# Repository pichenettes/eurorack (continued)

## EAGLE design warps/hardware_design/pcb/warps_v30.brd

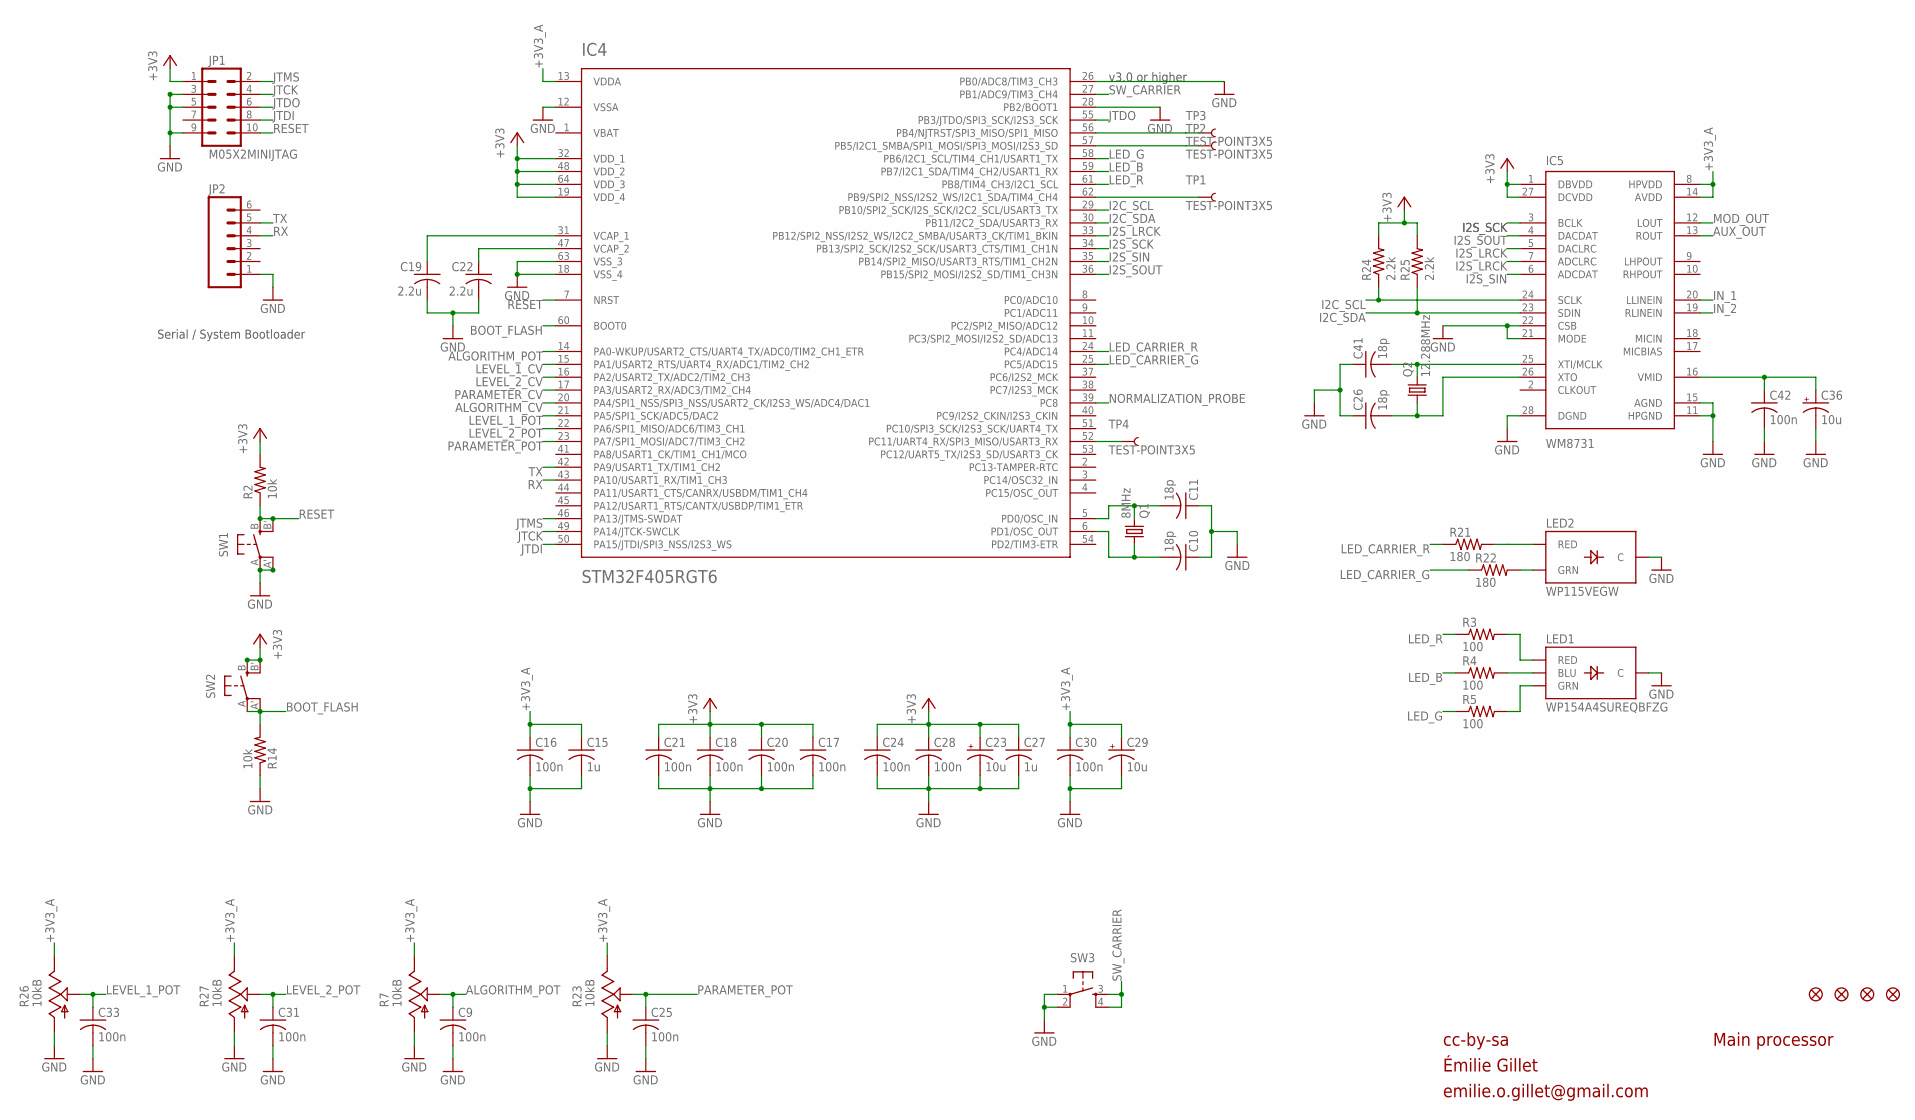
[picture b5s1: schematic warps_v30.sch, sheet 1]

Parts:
C9, C16, C17, C18, C20, C21, C24, C25, C28, C30, C31, C33, C42: 100n; C0603
C10, C11, C26, C41: 18p; C0603
C15, C27: 1u; C0603
C19, C22: 2.2u; C0805
C23, C29, C36: 10u; PANASONIC_A
F1, F2, F3, F4: FIDUCIAL1X2; FIDUCIAL-1X2
IC4: STM32F405RGT6; TQFP-10X10-64
IC5: WM8731; SSOP28
JP1: M05X2MINIJTAG; 2X5-1.27
JP2: M06SIP; 1X06
LED1: WP154A4SUREQBFZG; LED-TRICOLOR-THROUGHHOLE
LED2: WP115VEGW; LED-BICOLOR-THROUGHHOLE
Q1: 8MHz; HC49UP
Q2: 12.288MHz; HC49UP
R2, R14: 10k; R0603
R3, R4, R5: 100; R0603
R7, R23: 10kB; ALPS_POT_VERTICAL_PS
R21, R22: 180; R0603
R24, R25: 2.2k; R0603
R26, R27: 10kB; ALPS_POT_VERTICAL
SW1, SW2: EVQQ2; EVQ-Q2
SW3: TAC_SWITCHPTH; TACTILE-PTH
TP1, TP2, TP3, TP4: TEST-POINT3X5; PAD.03X.05

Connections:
+3V3: C17.1, C18.1, C20.1, C21.1, C23.+, C24.1, C27.1, C28.1, IC4.19 (VDD_4), IC4.32 (VDD_1), IC4.48 (VDD_2), IC4.64 (VDD_3), IC5.1 (DBVDD), IC5.27 (DCVDD), JP1.1, R2.2, R24.2, R25.2, SW2.B (S), SW2.B' (S1); also elsewhere on the board
+3V3_A: C15.1, C16.1, C29.+, C30.1, IC4.13 (VDDA), IC5.8 (HPVDD), IC5.14 (AVDD), R7.P$1 (E), R23.P$1 (E), R26.P$1 (E), R27.P$1 (E); also elsewhere on the board
ALGORITHM_CV: IC4.20 (PA4/SPI1_NSS/SPI3_NSS/USART2_CK/I2S3_WS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); also elsewhere on the board
ALGORITHM_POT: C9.1, IC4.14 (PA0-WKUP/USART2_CTS/UART4_TX/ADC0/TIM2_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), R7.P$2 (S)
AUX_OUT: IC5.13 (ROUT); also elsewhere on the board
BOOT_FLASH: IC4.60 (BOOT0), R14.2, SW2.A, SW2.A' (P1)
GND: C9.2, C10.1, C11.1, C15.2, C16.2, C17.2, C18.2, C19.2, C20.2, C21.2, C22.2, C23.-, C24.2, C25.2, C26.1, C27.2, C28.2, C29.-, C30.2, C31.2, C33.2, C36.-, C41.1, C42.2, IC4.12 (VSSA), IC4.18 (VSS_4), IC4.26 (PB0/ADC8/TIM3_CH3), IC4.28 (PB2/BOOT1), IC4.63 (VSS_3), IC5.11 (HPGND), IC5.15 (AGND), IC5.21 (MODE), IC5.22 (CSB), IC5.28 (DGND), JP1.3, JP1.5, JP1.9, JP2.1, LED1.GND (C), LED2.2 (C), R7.P$3 (A), R14.1, R23.P$3 (A), R26.P$3 (A), R27.P$3 (A), SW1.A, SW1.A' (P1), SW3.1, SW3.2; also elsewhere on the board
I2C_SCL: IC4.29 (PB10/SPI2_SCK/I2S_SCK/I2C2_SCL/USART3_TX), IC5.24 (SCLK), R24.1
I2C_SDA: IC4.30 (PB11/I2C2_SDA/USART3_RX), IC5.23 (SDIN), R25.1
I2S_LRCK: IC4.33 (PB12/SPI2_NSS/I2S2_WS/I2C2_SMBA/USART3_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), IC5.5 (DACLRC), IC5.7 (ADCLRC)
I2S_SCK: IC4.34 (PB13/SPI2_SCK/I2S2_SCK/USART3_CTS/TIM1_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), IC5.3 (BCLK)
I2S_SIN: IC4.35 (PB14/SPI2_MISO/USART3_RTS/TIM1_CH2N), IC5.6 (ADCDAT)
I2S_SOUT: IC4.36 (PB15/SPI2_MOSI/I2S2_SD/TIM1_CH3N), IC5.4 (DACDAT)
IN_1: IC5.20 (LLINEIN); also elsewhere on the board
IN_2: IC5.19 (RLINEIN); also elsewhere on the board
JTCK: IC4.49 (PA14/JTCK-SWCLK), JP1.4
JTDI: IC4.50 (PA15/JTDI/SPI3_NSS/I2S3_WS), JP1.8
JTDO: IC4.55 (PB3/JTDO/SPI3_SCK/I2S3_SCK), JP1.6
JTMS: IC4.46 (PA13/JTMS-SWDAT), JP1.2
LED_B: IC4.59 (PB7/I2C1_SDA/TIM4_CH2/USART1_RX), R4.1
LED_CARRIER_G: IC4.25 (PC5/ADC15), R22.1
LED_CARRIER_R: IC4.24 (PC4/ADC14), R21.1
LED_G: IC4.58 (PB6/I2C1_SCL/TIM4_CH1/USART1_TX), R5.1
LED_R: IC4.61 (PB8/TIM4_CH3/I2C1_SCL), R3.1
LEVEL_1_CV: IC4.15 (PA1/USART2_RTS/UART4_RX/ADC1/TIM2_CH2); also elsewhere on the board
LEVEL_1_POT: C33.1, IC4.21 (PA5/SPI1_SCK/ADC5/DAC2), R26.P$2 (S)
LEVEL_2_CV: IC4.16 (PA2/USART2_TX/ADC2/TIM2_CH3); also elsewhere on the board
LEVEL_2_POT: C31.1, IC4.22 (PA6/SPI1_MISO/ADC6/TIM3_CH1), R27.P$2 (S)
MOD_OUT: IC5.12 (LOUT); also elsewhere on the board
unnamed: LED2.3 (RED), R21.2
unnamed: C11.2, IC4.5 (PD0/OSC_IN), Q1.2
unnamed: C10.2, IC4.6 (PD1/OSC_OUT), Q1.1
unnamed: C22.1, IC4.47 (VCAP_2)
unnamed: LED2.1 (GRN), R22.2
unnamed: C36.+, C42.1, IC5.16 (VMID)
unnamed: C19.1, IC4.31 (VCAP_1)
unnamed: IC4.56 (PB4/NJTRST/SPI3_MISO/SPI1_MISO), TP3.P$1
unnamed: IC4.57 (PB5/I2C1_SMBA/SPI1_MOSI/SPI3_MOSI/I2S3_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), TP2.P$1
unnamed: IC4.52 (PC11/UART4_RX/SPI3_MISO/USART3_RX), TP4.P$1
unnamed: IC4.62 (PB9/SPI2_NSS/I2S2_WS/I2C1_SDA/TIM4_CH4), TP1.P$1
unnamed: LED1.RED, R3.2
unnamed: LED1.BLU, R4.2
unnamed: LED1.GRN, R5.2
unnamed: C41.2, IC5.25 (XTI/MCLK), Q2.2
unnamed: C26.2, IC5.26 (XTO), Q2.1
NORMALIZATION_PROBE: IC4.39 (PC8); also elsewhere on the board
PARAMETER_CV: IC4.17 (PA3/USART2_RX/ADC3/TIM2_CH4); also elsewhere on the board
PARAMETER_POT: C25.1, IC4.23 (PA7/SPI1_MOSI/ADC7/TIM3_CH2), R23.P$2 (S)
RESET: IC4.7 (NRST), JP1.10, R2.1, SW1.B (S), SW1.B' (S1)
RX: IC4.43 (PA10/USART1_RX/TIM1_CH3), JP2.4
SW_CARRIER: IC4.27 (PB1/ADC9/TIM3_CH4), SW3.3, SW3.4
TX: IC4.42 (PA9/USART1_TX/TIM1_CH2), JP2.5
VBAT: IC4.1 (VBAT)

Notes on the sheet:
cc-by-sa
Main processor
Serial / System Bootloader
v3.0 or higher
Émilie Gillet
emilie.o.gillet@gmail.com

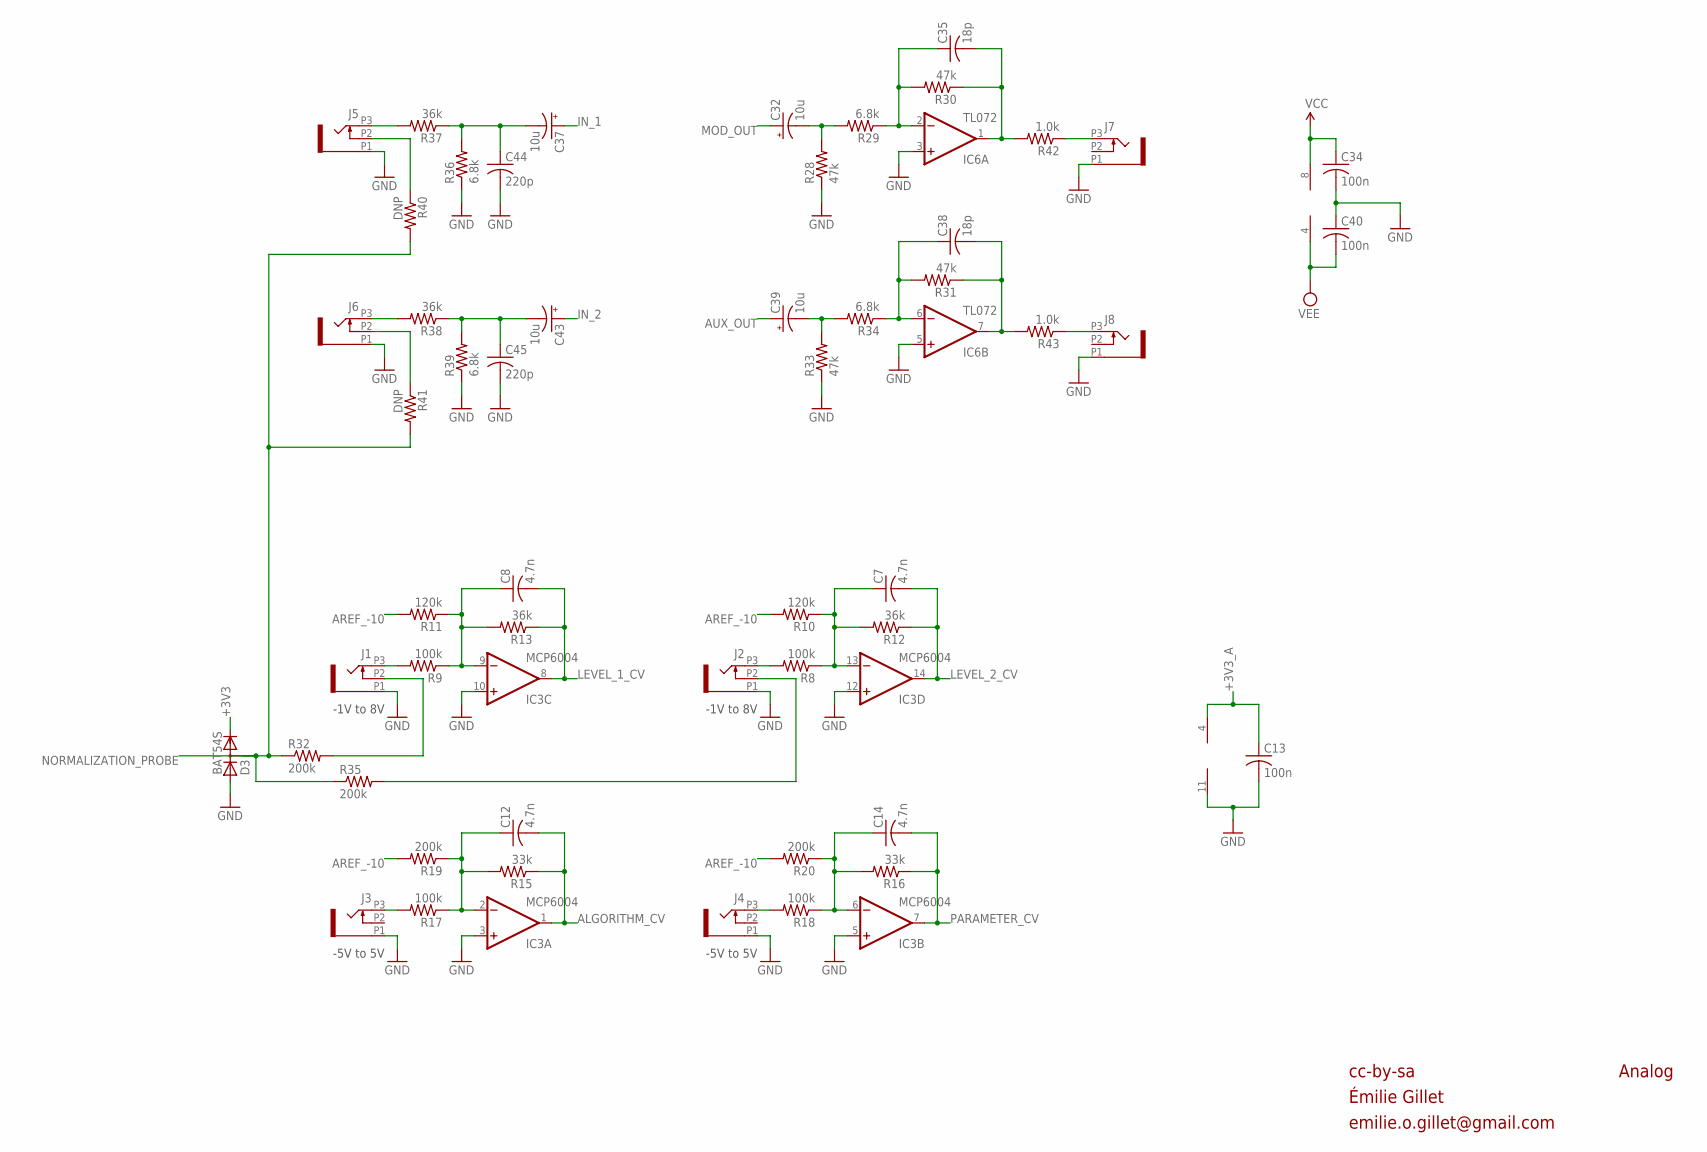
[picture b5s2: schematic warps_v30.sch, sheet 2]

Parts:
C7, C8, C12, C14: 4.7n; C0603
C13, C34, C40: 100n; C0603
C32, C37, C39, C43: 10u; PANASONIC_A
C35, C38: 18p; C0603
C44, C45: 220p; C0603
D3: BAT54S; SOT23
IC3: MCP6004; SO14
IC6: TL072; SO08
J1, J2, J3, J4, J5, J6, J7, J8: PJ301_THONKICONN6; WQP_PJ_301M6
R8, R9, R17, R18: 100k; R0603
R10, R11: 120k; R0603
R12, R13, R37, R38: 36k; R0603
R15, R16: 33k; R0603
R19, R20, R32, R35: 200k; R0603
R28, R30, R31, R33: 47k; R0603
R29, R34, R36, R39: 6.8k; R0603
R40, R41: DNP; R0603
R42, R43: 1.0k; R0603

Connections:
+3V3: D3.2 (C); also elsewhere on the board
+3V3_A: C13.1, IC3.4 (V+); also elsewhere on the board
ALGORITHM_CV: C12.2, IC3.1 (OUT), R15.1; also elsewhere on the board
AREF_-10: R10.2, R11.2, R19.2, R20.2; also elsewhere on the board
AUX_OUT: C39.+; also elsewhere on the board
GND: C13.2, C34.2, C40.1, C44.2, C45.2, D3.1 (A), IC3.3 (+IN), IC3.5 (+IN), IC3.10 (+IN), IC3.11 (V-), IC3.12 (+IN), IC6.3 (+IN), IC6.5 (+IN), J1.P1 (1), J2.P1 (1), J3.P1 (1), J4.P1 (1), J5.P1 (1), J6.P1 (1), J7.P1 (1), J8.P1 (1), R28.1, R33.1, R36.1, R39.1; also elsewhere on the board
IN_1: C37.+; also elsewhere on the board
IN_2: C43.+; also elsewhere on the board
LEVEL_1_CV: C8.2, IC3.8 (OUT), R13.1; also elsewhere on the board
LEVEL_2_CV: C7.2, IC3.14 (OUT), R12.1; also elsewhere on the board
MOD_OUT: C32.+; also elsewhere on the board
unnamed: J1.P3 (3), R9.2
unnamed: C8.1, IC3.9 (-IN), R9.1, R11.1, R13.2
unnamed: J2.P3 (3), R8.2
unnamed: C7.1, IC3.13 (-IN), R8.1, R10.1, R12.2
unnamed: J4.P3 (3), R18.2
unnamed: J1.P2 (2), R32.2
unnamed: J3.P3 (3), R17.2
unnamed: C12.1, IC3.2 (-IN), R15.2, R17.1, R19.1
unnamed: J2.P2 (2), R35.2
unnamed: C14.1, IC3.6 (-IN), R16.2, R18.1, R20.1
unnamed: C37.-, C44.1, R36.2, R37.1
unnamed: J6.P3 (3), R38.2
unnamed: J5.P3 (3), R37.2
unnamed: C43.-, C45.1, R38.1, R39.2
unnamed: C39.-, R33.2, R34.2
unnamed: C38.1, IC6.6 (-IN), R31.2, R34.1
unnamed: C38.2, IC6.7 (OUT), R31.1, R43.2
unnamed: J8.P3 (3), R43.1
unnamed: C32.-, R28.2, R29.2
unnamed: C35.1, IC6.2 (-IN), R29.1, R30.2
unnamed: C35.2, IC6.1 (OUT), R30.1, R42.2
unnamed: J7.P3 (3), R42.1
unnamed: J6.P2 (2), R41.1
unnamed: J5.P2 (2), R40.1
NORMALIZATION_PROBE: D3.3 (AC), R32.1, R35.1, R40.2, R41.2; also elsewhere on the board
PARAMETER_CV: C14.2, IC3.7 (OUT), R16.1; also elsewhere on the board
VCC: C34.1, IC6.8 (V+); also elsewhere on the board
VEE: C40.2, IC6.4 (V-); also elsewhere on the board

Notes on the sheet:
cc-by-sa
Analog
-1V to 8V
-5V to 5V
Émilie Gillet
emilie.o.gillet@gmail.com

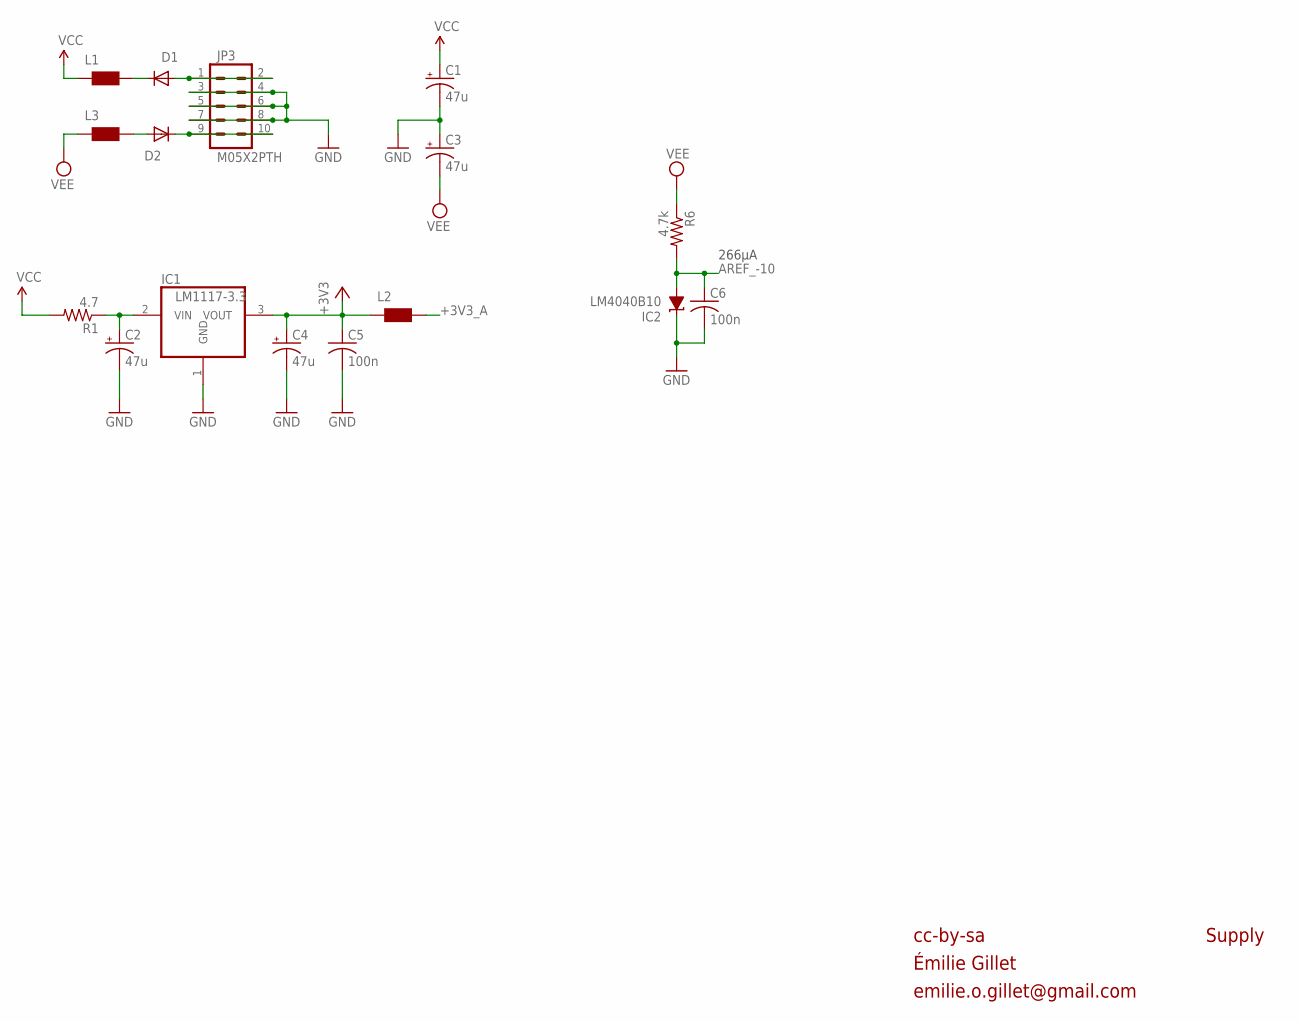
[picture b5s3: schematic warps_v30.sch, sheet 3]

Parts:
C1, C2, C3, C4: 47u; PANASONIC_D
C5, C6: 100n; C0603
D1, D2: 1N5819HW; SOD123
IC1: LM1117-3.3; TO252
IC2: LM4040B10; DBZ_R-PDSO-G3
JP3: M05X2PTH; AVR_ICSP
L1, L2, L3: WE-CBF_0603; 0603
R1: 4.7; R1206
R6: 4.7k; R0603

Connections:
+3V3: C4.+, C5.1, IC1.3 (VOUT), L2.1; also elsewhere on the board
+3V3_A: L2.2; also elsewhere on the board
AREF_-10: C6.1, IC2.2 (A), R6.2; also elsewhere on the board
GND: C1.-, C2.-, C3.+, C4.-, C5.2, C6.2, IC1.1 (GND), IC2.1 (C), JP3.3, JP3.4, JP3.5, JP3.6, JP3.7, JP3.8; also elsewhere on the board
unnamed: C2.+, IC1.2 (VIN), R1.1
unnamed: D1.C, L1.2
unnamed: D2.A, L3.2
unnamed: D1.A, JP3.1, JP3.2
unnamed: D2.C, JP3.9, JP3.10
VCC: C1.+, L1.1, R1.2; also elsewhere on the board
VEE: C3.-, L3.1, R6.1; also elsewhere on the board

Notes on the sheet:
266µA
cc-by-sa
Supply
Émilie Gillet
emilie.o.gillet@gmail.com

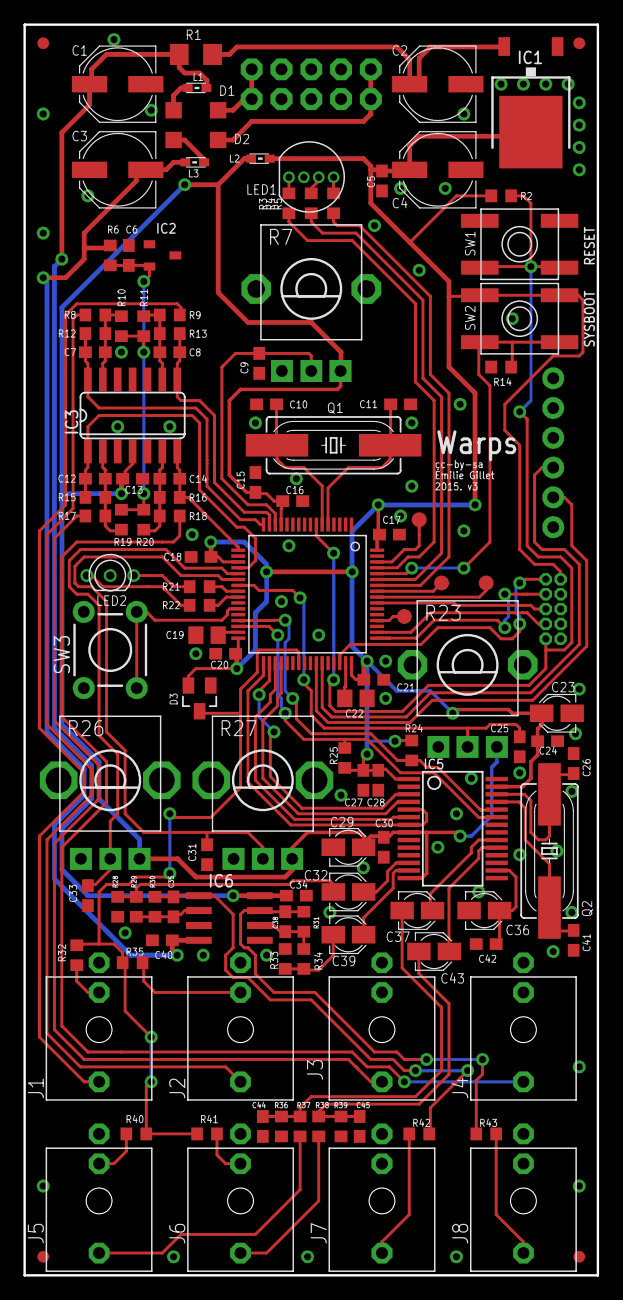
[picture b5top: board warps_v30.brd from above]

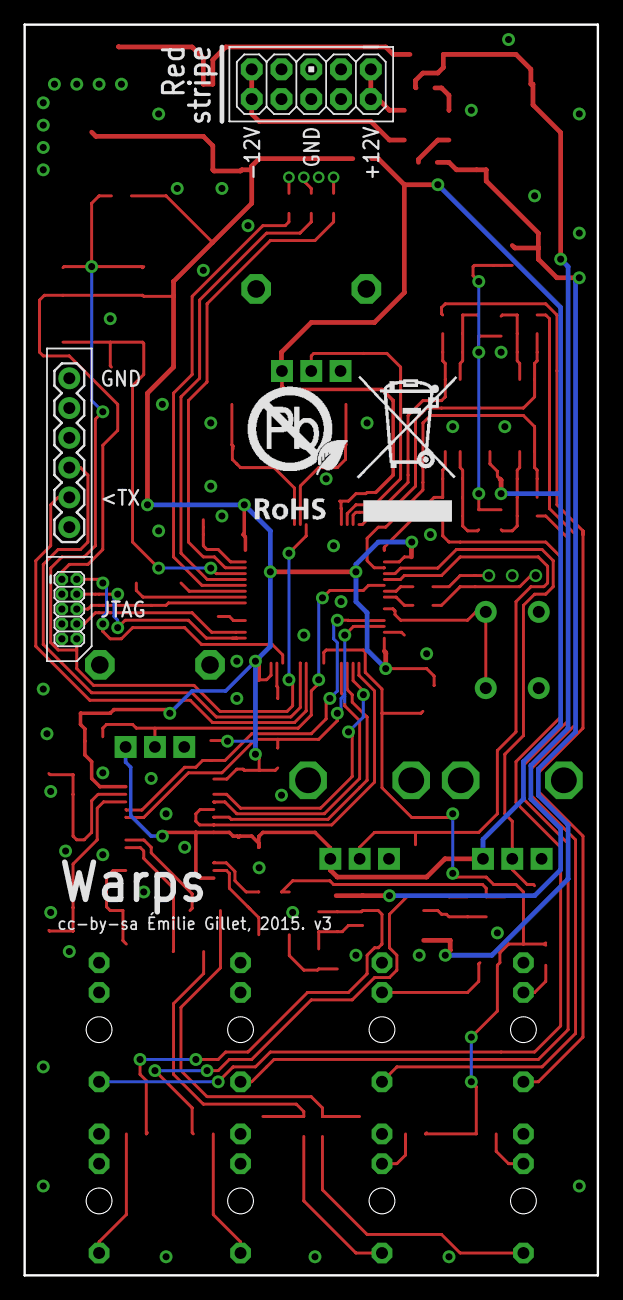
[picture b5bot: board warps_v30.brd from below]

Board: 2 copper layers, 48.9 x 106.7 mm, 127 parts (4 on the bottom side), 84 nets.

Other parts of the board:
U$2: ROHS_BIG

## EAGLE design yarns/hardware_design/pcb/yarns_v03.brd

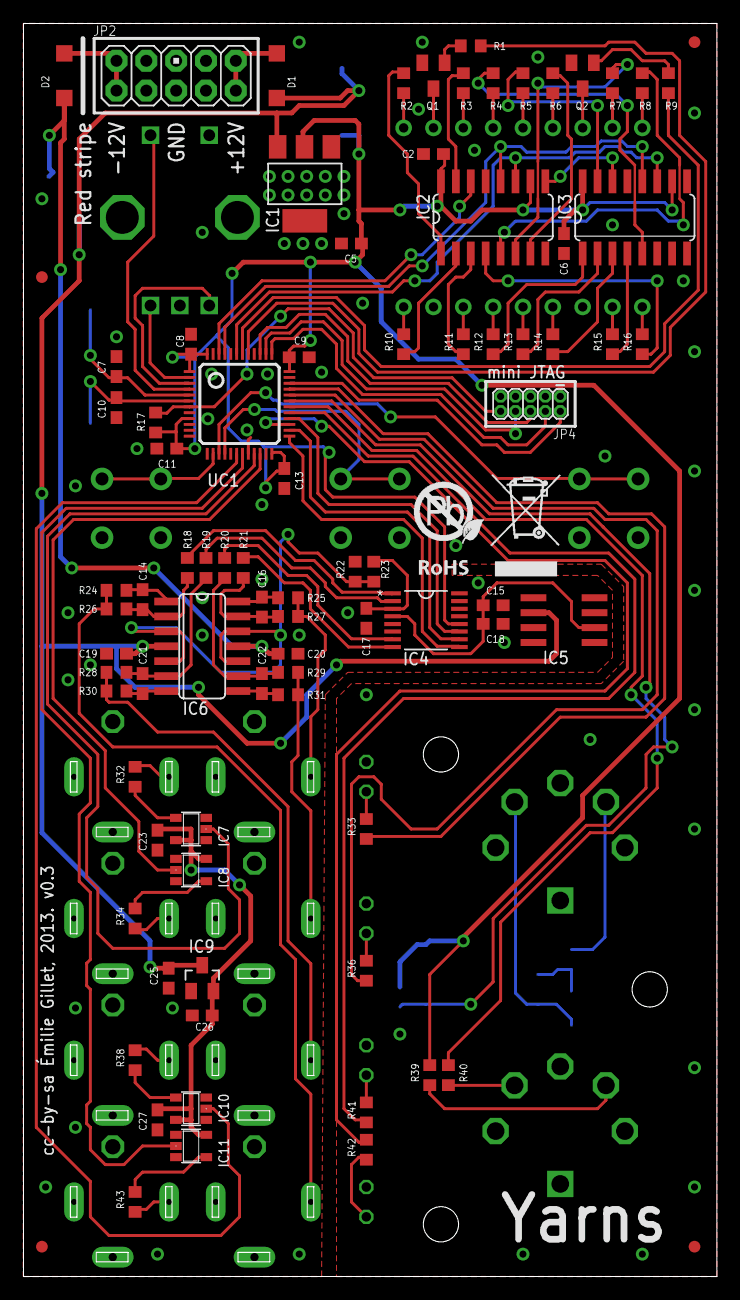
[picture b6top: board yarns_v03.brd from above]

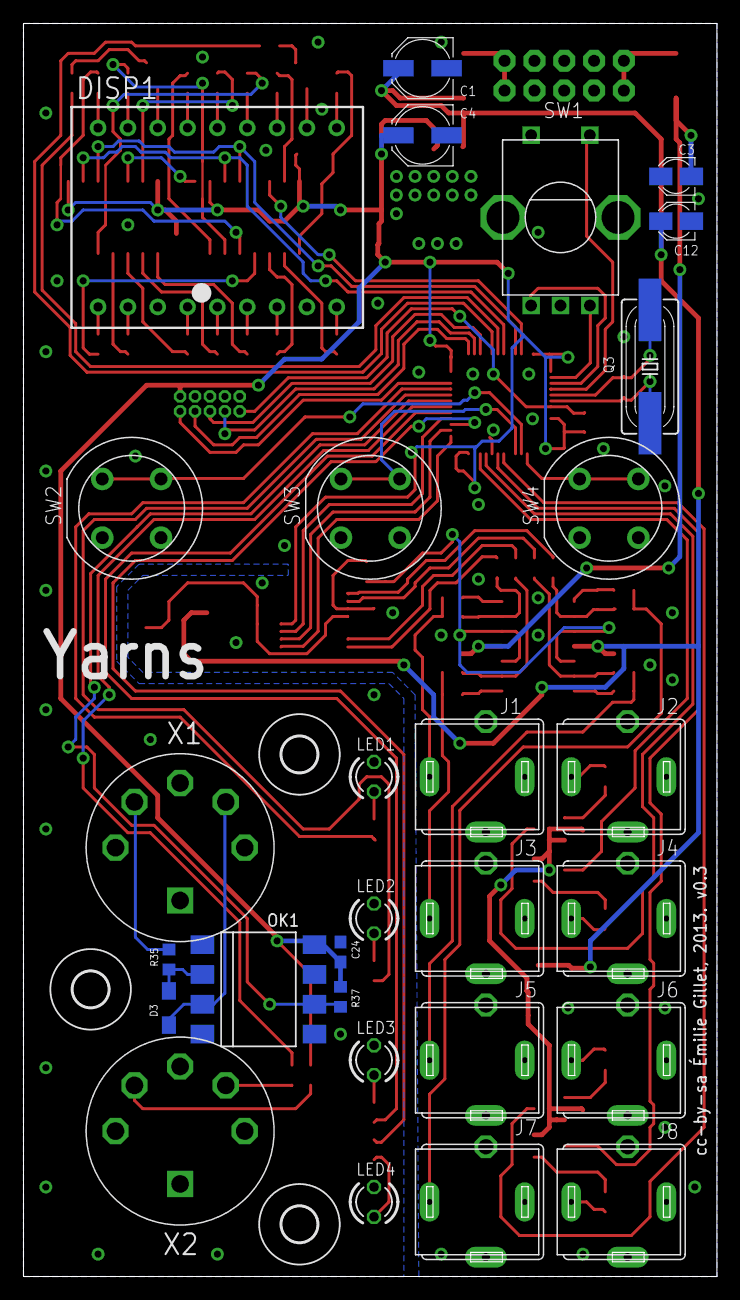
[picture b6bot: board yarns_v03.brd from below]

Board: 2 copper layers, 59.0 x 106.7 mm, 118 parts (32 on the bottom side), 107 nets.

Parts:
C1, C4: 22u; PANASONIC_C
C2, C5, C6, C8, C9, C11, C13, C18, C19, C20, C23, C24, C27: 100n; C0603
C3, C12: 10u; PANASONIC_A
C7, C10, C14, C16, C21, C22: 18p; C0603
C15: 3.3u; C0603
C17: 220n; C0603
C25, C26: 1u; C0603
D1, D2: 1N5819HW; SOD123
D3: 1N4148; SOD323-W
DISP1: KINGBRIGHT-PDC54-11; PDC54
F1, F3, F5, F6: FIDUCIAL1X2; FIDUCIAL-1X2
IC1: LM1117-3.3; SOT223
IC2, IC3: 74HC595D; SO16
IC4: DAC8564; SOP65P640X110-16N
IC5: REF02D; SO08
IC6: OPA4171; SO14
IC7, IC8, IC10, IC11: 74AHCT1G125DBV; SOT23-5
IC9: MCP1703CB; SOT23
J1, J2, J3, J4, J5, J6, J7, J8: PJ301WQP; WQP_PJ_301BM
JP2: M05X2PTH; AVR_ICSP
JP4: 2X5-1.27
LED1, LED2, LED3, LED4: LED3MM
OK1: 6N137SMT; DIL8-SMD
Q1, Q2: MMBT3904; SOT23-BEC
Q3: 8MHz; HC49UP
R1, R9, R24, R25, R30, R31, R32, R34, R38, R43: 1.0k; R0603
R2, R3, R4, R5, R6, R7, R8, R10, R11, R12, R13, R14, R15, R16, R33, R36, R41, R42: 100; R0603
R17, R37: 10k; R0603
R18, R19, R20, R21, R22, R23: 47k; R0603
R26, R27, R28, R29: 240k; R0603
R35: 220; R0603
R39, R40: 51; R0603
SW1: EC12E_SW; ALPS_EC12E_SW
SW2: D6R40F2LFS; D6R
SW3, SW4: D6R
U$2, U$3, U$4: 3,0
U$5: ROHS
UC1: STM32F103CBT6; LQFP48
X1, X2: CUI-SD-50BV; SD-50BV

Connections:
+3V3: C2.1, C4.+, C5.1, C6.1, C8.1, C9.1, C11.1, C13.1, C24.1, IC1.2, IC2.10, IC2.16, IC3.10, IC3.16, IC4.12, JP4.1, OK1.8, R17.2, R37.2, R39.2, UC1.1, UC1.9, UC1.24, UC1.36, UC1.48
+5V: C15.1, C18.1, IC4.4, IC5.6
+5VD: C23.1, C26.1, C27.1, IC7.5, IC8.5, IC9.2, IC10.5, IC11.5
AOUT: J2.TIP, R32.1
CH_A: IC4.1, R18.2
CH_B: IC4.2, R19.2
CH_C: IC4.7, R20.2
CH_D: IC4.8, R21.2
DAC_MOSI: IC4.11, UC1.28
DAC_SCK: IC4.10, UC1.26
DAC_SS: IC4.9, UC1.25
DISP_CHAR0: R9.1, UC1.42
DISP_CHAR1: R1.1, UC1.41
DISP_EN: IC2.12, IC3.12, UC1.45
DISP_SCK: IC2.11, IC3.11, UC1.43
DISP_SER: IC2.14, UC1.46
ENC_A: SW1.B, UC1.2
ENC_B: SW1.A, UC1.3
ENC_CLICK: SW1.E, UC1.4
GATE_A: IC7.2, UC1.21
GATE_B: IC8.2, UC1.22
GATE_C: IC10.2, UC1.18
GATE_D: IC11.2, UC1.19
GND: C1.-, C2.2, C3.+, C4.-, C5.2, C6.2, C7.1, C8.2, C9.2, C10.1, C11.2, C12.-, C13.2, C15.2, C17.2, C18.2, C19.2, C20.1, C23.2, C24.2, C25.2, C26.2, C27.2, IC1.1, IC2.8, IC2.13, IC3.8, IC3.13, IC4.5, IC4.6, IC4.13, IC4.14, IC4.15, IC4.16, IC5.4, IC7.1, IC7.3, IC8.1, IC8.3, IC9.1, IC10.1, IC10.3, IC11.1, IC11.3, J1.GND, J1.GND2, J2.GND, J2.GND2, J3.GND, J3.GND2, J4.GND, J4.GND2, J5.GND, J5.GND2, J6.GND, J6.GND2, J7.GND, J7.GND2, J8.GND, J8.GND2, JP2.3, JP2.4, JP2.5, JP2.6, JP2.7, JP2.8, JP4.3, JP4.5, JP4.9, LED1.K, LED2.K, LED3.K, LED4.K, OK1.5, Q1.E, Q2.E, R22.1, SW1.C, SW1.D, SW2.B1, SW2.B2, SW3.B1, SW3.B2, SW4.B1, SW4.B2, UC1.8, UC1.20, UC1.23, UC1.35, UC1.44, UC1.47, X2.2
JTCK: JP4.4, UC1.37
JTDI: JP4.8, UC1.38
JTDO: JP4.6, UC1.39
JTMS: JP4.2, UC1.34
LED_1: R33.1, UC1.33
LED_2: R36.1, UC1.32
LED_3: R41.1, UC1.29
LED_4: R42.1, UC1.27
MIDI_RX: OK1.6, R37.1, UC1.31
MIDI_TX: R40.2, UC1.30
unnamed: DISP1.16, Q2.C
unnamed: C22.1, IC6.9, R20.1, R29.2
unnamed: DISP1.11, Q1.C
unnamed: C7.2, Q3.2, UC1.5
unnamed: C10.2, Q3.1, UC1.6
unnamed: Q2.B, R9.2
unnamed: Q1.B, R1.2
unnamed: D3.C, OK1.2, R35.1
unnamed: R35.2, X1.4
unnamed: R40.1, X2.5
unnamed: DISP1.17, R7.2
unnamed: D3.A, OK1.3, X1.5
unnamed: R39.1, X2.4
unnamed: IC7.4, R32.2
unnamed: DISP1.12, R3.2
unnamed: DISP1.10, R2.2
unnamed: DISP1.9, R10.2
unnamed: DISP1.7, R11.2
unnamed: DISP1.1, R16.2
unnamed: DISP1.18, R8.2
unnamed: DISP1.15, R6.2
unnamed: DISP1.14, R5.2
unnamed: DISP1.6, R12.2
unnamed: DISP1.5, R13.2
unnamed: DISP1.4, R14.2
unnamed: DISP1.2, R15.2
unnamed: DISP1.13, R4.2
unnamed: IC8.4, R34.2
unnamed: IC2.7, R6.1
unnamed: IC2.9, IC3.14
unnamed: IC2.15, R3.1
unnamed: IC2.1, R2.1
unnamed: IC2.2, R10.1
unnamed: IC2.3, R11.1
unnamed: IC2.4, R16.1
unnamed: IC2.5, R8.1
unnamed: IC2.6, R7.1
unnamed: IC3.15, R5.1
unnamed: IC3.1, R12.1
unnamed: IC3.2, R13.1
unnamed: IC3.3, R14.1
unnamed: IC3.4, R15.1
unnamed: IC3.5, R4.1
unnamed: IC10.4, R38.2
unnamed: IC11.4, R43.2
unnamed: C14.2, IC6.1, R24.2
unnamed: J6.TIP, R38.1
unnamed: J8.TIP, R43.1
unnamed: C21.2, IC6.7, R30.2
unnamed: C22.2, IC6.8, R31.2
unnamed: C16.2, IC6.14, R25.2
unnamed: J7.TIP, R24.1, R26.1
unnamed: LED1.A, R33.2
unnamed: J3.TIP, R29.1, R31.1
unnamed: D1.A, JP2.1, JP2.2
unnamed: J4.TIP, R34.1
unnamed: J1.TIP, R25.1, R27.1
unnamed: C16.1, IC6.13, R21.1, R27.2
unnamed: C21.1, IC6.6, R19.1, R28.2
unnamed: C14.1, IC6.2, R18.1, R26.2
unnamed: J5.TIP, R28.1, R30.1
unnamed: D2.C, JP2.9, JP2.10
unnamed: LED2.A, R36.2
unnamed: LED3.A, R41.2
unnamed: LED4.A, R42.2
RESET: JP4.10, R17.1, UC1.7
SWITCH_0: SW2.A1, SW2.A2, UC1.15
SWITCH_1: SW3.A1, SW3.A2, UC1.16
SWITCH_2: SW4.A1, SW4.A2, UC1.14
VCC: C1.+, C12.+, C19.1, C25.1, D1.C, IC1.3, IC5.2, IC6.4, IC9.3
VEE: C3.-, C20.2, D2.A, IC6.11
VREF: C17.1, IC4.3, R23.2
VREF/2: IC6.3, IC6.5, IC6.10, IC6.12, R22.2, R23.1
